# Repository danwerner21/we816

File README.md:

# WE816
The WE816 is a 16-bit 65816 based system with 512K of System RAM, 96K of System ROM, 32K of video RAM, a TMS9918 graphics processor and an AY-3-8910 Sound chip.  The system runs a custom version of BASIC and supports commodore compatible IEC disk drives.

EhBASIC by Lee Davison was ported to the 65816 CPU on the WE816 computer.   It is designed to allow a full 64K bank for BASIC code and variables with the BASIC interpreter running in a totally different bank. Full documentation on the basic intrepreter can be found in the support folder

---

## To Do:

* RTC Hardware (fixed needs PCB created and tested)

* BIOS RTC Code

* Basic Access to RTC

* Fix Video RAM paging

* Document BIOS Calls

---

## What is included in this repo?
As of this time, the repo includes

1. The WE816 Mainboard PCB Kicad design and Gerber files
2. The source code and binaries for the WE816 BASIC interpreter
3. The source code and binaries for the WE816 BIOS firmware
4. The source code and binaries for several hardware test programs
5. The logic equasions for the 3 GALs
6. **OpenSCAD and STL files for a 3d printed case

---

## Known Bugs

 * Note that the Real Time clock circuit on the 8/5/2021 .85 verson of the board is broken and will not work.  The schematic in this repo has been updated to a working version, but this board still has U12 Pin 6 & 7  connected to CB1 & 2 of U36 which has a broken shift register implementation.   I was under the mistaken impression that the shift register bug had been corrected on the WDC version of the 6522, but this is not the case.

### System Jumpers

Jumper P9 -- stereo channel mixer

 *  no jumpers, channel a left, channel c right, channel b left and right
 *  1-2 and 2-3 , channel a,b,c mixed to left and right

Jumper K1 - SRAM chip selection

 * 1&2 - 512K chip used (AS6C4008)
 * 2&3 - 128K chip used (AS6C1008)

Jumper K2 - ROM chip selection

 * 1&2 - 27c256 chip used
 * 2&3 - 29c256 chip used

Jumper K3 - ROM size

 * 1&2 - 16K rom page 0 memory map @ $C000
 * 2&3 - 32K rom page 0 memory map @ $8000

Power P1

 * 1- NC
 * 2-GND
 * 3-GND
 * 4-+5VDC 2A Regulated

Reset P2

 * NO Switch (Short to put system in reset)

Jumper J1, Interrupt Select

* 1&8 UART Interrupt enabled
* 2&7 VIA 1 Interrupt enabled
* 3&6 VIA 2 Interrupt enabled
* 4&5 TMS9918 Interrupt enabled

---

## Bill Of Materials

### Mainboard

Qty|Reference(s)|Value
--------|--------|----------
1|BT1|Battery_Cell
35|C1-C33, C37, C49|0.1 uF
2|C34, C35|33 pF
2|C36, C48|22 uF
1|C38|220 uF
5|C39-C43|1.0 uF
2|C44, C45|270 pF
3|C46, C47, C50|10 uF
1|D1|BICOLOR LED
1|J1|Conn_01x02_Male
1|J2|Conn_01x06_Male
1|J3|Conn_02x08_Counter_Clockwise
1|J4|DIN-5
1|J5|Conn_01x03_Male
1|J6|Conn_02x04_Counter_Clockwise
1|J7|Conn_02x20_Odd_Even
1|J8|AudioJack3
2|J9, J10|DB9_Male
1|K1|Conn_01x03_Male
1|K2|Conn_01x03_Male
1|K3|Conn_01x03_Male
1|L1|INDUCTOR (BEAD)
1|P1|Conn_02x05_Odd_Even
1|P2|Conn_02x02_Odd_Even
1|P3|Screw_Terminal_01x02
1|P4|Conn_01x02_Male
1|P5|Oscillator:CXO_DIP8
1|Q1|2N3904
1|R1|0 ohm
1|R2|470 ohm
2|R3, R4|75 ohm
3|R5, R6, R7|1K ohm
4|R8, R9, R10, R18|1K ohm
5|R11, R12, R13, R14, R17|10K ohm
1|R15|100 ohm
1|R16|10 ohm
1|RR1|1K ohm Bussed 6 pin
2|RR2, RR3|4700 ohm Bussed 6 pin
1|RR4|4700 ohm Bussed 10 pin
2|RV1, RV2|4700 ohm variable
1|U1|74LS393
1|U2|7406
1|U3|74LS06N
1|U4|74F14  (should be F)
1|U5|74LS04
1|U6|TMS9918
1|U7|74LS574
2|U8, U9|74LS574
1|U10|RAM_32KO
1|U11|74LS32
2|U12, U14|GAL16V8 (7ns)
1|U13|GAL20V8 (7ns)
1|U15|16550
1|U16|DS1302
1|U17|MAX232
2|U18, U19|W65C22NxP
5|U20, U22, U23, U24, U31|74LS245
1|U21|74LS244
1|U25|AY-3-8910
1|U26|SRAM_512KO
1|U27|658C16
1|U28|27C256
1|U29|27C512
1|U30|74LS373
1|X1|10.7 MHz
1|X2|CXO_DIP8
1|X3|CRYSTAL 32.768 KHz

### Keyboard
The Keyboard used in the WE816 is identical to the keyboard used in Sergey Kiselev's MSX compatible OMEGA computer.  See the Schematics, PCB layout and build instructions
[here](https://github.com/skiselev/omega/blob/master/Keyboard.md)

### Case
The case in the following images is a 3D print manufactured by the 3D print service offered by JLCPCB.com.  The case was originally designed to be 3D printed by a FDM printer such as the Anycubic Chiron.   It was originally intended that threaded inserts be melted into the stand off posts so the diameter of the holes were sized accordingly.  If a printing service (such as JLCPCB) is used that uses resin printing, it is necessary to slightly drill out the holes in the stand offs so that threaded inserts can be glued in.   It should also be noted that the design tolerances are quite tight and variations in printing can mean that some slight adjusting may be needed in order to get a good fit.

A 12V to 5V converter can be seen in the image that was added into the case in order to convert the 12V power input to the 5B required by the main board.

### Questions?

If there are any questions, I can be reached at vic2020Dan at gmail dot com.

---

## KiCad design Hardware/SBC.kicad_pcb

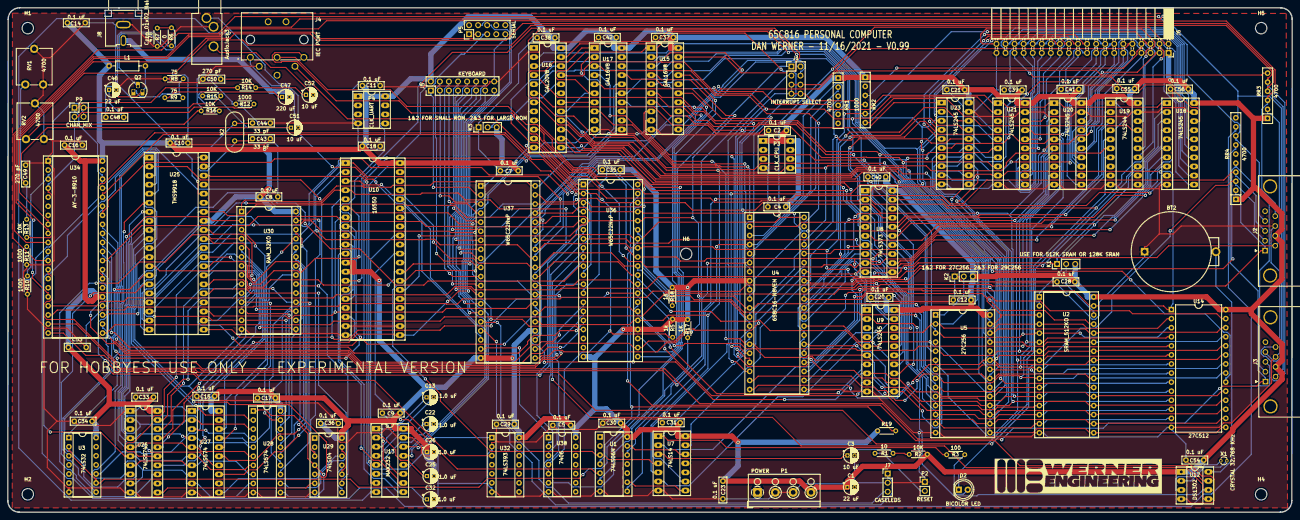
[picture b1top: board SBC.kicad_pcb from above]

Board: 2 copper layers, 360.1 x 141.4 mm, 135 parts (0 on the bottom side), 249 nets.

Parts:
BT2: Battery_Cell; Battery_Holder_Coin_2032_BS-7_FIXED
C1, C46: 22 uF; CP_Radial_D4.0mm_P2.00mm
C2, C4, C5, C7, C8, C9, C10, C11, C12, C14, C15, C16, C17, C18, C20, C21, C23, C28, C29, C30, C31, C33, C34, C35, C36, C37, C38, C39, C40, C41, C42, C48, C53, C54, C55, C56: 0.1 uF; C_Rect_L7.0mm_W2.0mm_P5.00mm
C3, C51, C52: 10 uF; CP_Radial_D4.0mm_P2.00mm
C13, C22, C25, C26, C32: 1.0 uF; CP_Radial_D4.0mm_P2.00mm
C43, C44: 33 pF; C_Rect_L7.0mm_W2.0mm_P5.00mm
C47: 220 uF; CP_Radial_D4.0mm_P2.00mm
C49, C50: 270 pF; C_Rect_L7.0mm_W2.0mm_P5.00mm
D2: BICOLOR LED; LED_D5.0mm
H1, H2, H4, H5, H6: MountingHole; MountingHole_3.2mm_M3
J1: INTERRUPT SELECT; PinHeader_2x04_P2.54mm_Vertical
J2, J3: DB9_Male; DSUB-9_Male_Horizontal_P2.77x2.84mm_EdgePinOffset9.90mm_Hou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
J4: IEC PORT; din6
J5: KEYBOARD; PinHeader_2x08_P2.54mm_Vertical_FIXED
J6: expansion port; PinSocket_2x20_P2.54mm_Horizontal
J7: CASELEDS; PinHeader_1x03_P2.54mm_Vertical
J8: Conn_01x02_Male; CUI_RCJ-041
J9: AudioJack3; Jack_3.5mm_CUI_SJ1-3533NG_Horizontal_CircularHoles
K1: USE FOR 512K SRAM OR 128K SRAM; PinHeader_1x03_P2.54mm_Vertical
K2: 1&2 FOR 27C256, 2&3 FOR 29C256; PinHeader_1x03_P2.54mm_Vertical
K3: 1&2 FOR SMALL ROM, 2&3 FOR LARGE ROM; PinHeader_1x03_P2.54mm_Vertical
L1: INDUCTOR (BEAD); R_Axial_DIN0207_L6.3mm_D2.5mm_P10.16mm_Horizontal
P1: POWER; TerminalBlock_RND_205-00003_1x04_P5.00mm_Horizontal
P2: RESET; PinHeader_1x02_P2.54mm_Vertical
P3: CLK_CPU; DIP-8_W7.62mm_Socket_LongPads
P4: CLK_UART; DIP-8_W7.62mm_Socket_LongPads
P5: SERIAL; PinHeader_2x05_P2.54mm_Vertical
P9: CHAN_MIX; PinHeader_2x02_P2.54mm_Vertical
Q2: 2N3904; TO-92L_HandSolder
R1: 10; R_Axial_DIN0204_L3.6mm_D1.6mm_P5.08mm_Horizontal
R2, R13, R14, R15, R16: 10K; R_Axial_DIN0204_L3.6mm_D1.6mm_P5.08mm_Horizontal
R3: 100; R_Axial_DIN0204_L3.6mm_D1.6mm_P5.08mm_Horizontal
R5: 1k; R_Axial_DIN0204_L3.6mm_D1.6mm_P5.08mm_Horizontal
R6: 0; R_Axial_DIN0204_L3.6mm_D1.6mm_P5.08mm_Horizontal
R7: 470; R_Axial_DIN0204_L3.6mm_D1.6mm_P5.08mm_Horizontal
R8, R9: 75; R_Axial_DIN0204_L3.6mm_D1.6mm_P5.08mm_Horizontal
R10, R11, R12: 1000; R_Axial_DIN0204_L3.6mm_D1.6mm_P5.08mm_Horizontal
R17, R18, R19: 1K; R_Axial_DIN0204_L3.6mm_D1.6mm_P5.08mm_Horizontal
RR1, RR3: 4700; R_Array_SIP6
RR2: 1000; R_Array_SIP6
RR4: 4700; R_Array_SIP10
RV1, RV2: 4700; Potentiometer_ACP_CA9-V10_Vertical
U1: 74LS06N; DIP-14_W7.62mm_Socket
U2: SRAM_512KO; DIP-32_W15.24mm_Socket
U3: 74LS32; DIP-14_W7.62mm_Socket
U4: 658C16-N8VEM; DIP-40_W15.24mm_Socket
U5: 27C256; DIP-28_W15.24mm_Socket
U7: 74LS14; DIP-14_W7.62mm_Socket_LongPads
U8: 74LS373; DIP-20_W7.62mm_Socket_LongPads
U9, U18, U20, U21, U23: 74LS245; DIP-20_W7.62mm_Socket_LongPads
U10: 16550; DIP-40_W15.24mm_Socket_LongPads
U12: DS1302; DIP-8_W7.62mm_Socket_LongPads
U13: MAX232; DIP-16_W7.62mm_Socket_LongPads
U14: 27C512; DIP-28_W15.24mm
U15, U17: GAL16V8; DIP-20_W7.62mm_Socket_LongPads
U16: GAL20V8; DIP-24_W7.62mm_Socket_LongPads
U19: 74LS244; DIP-20_W7.62mm_Socket_LongPads
U25: TMS9918; DIP-40_W15.24mm_Socket_LongPads
U26, U27: 74LS574; DIP-20_W7.62mm_Socket_LongPads
U28: 74LS574; DIP-20_W7.62mm_Socket
U29: 74LS04; DIP-14_W7.62mm_Socket
U30: RAM_32KO; DIP-28_W15.24mm_Socket
U32: 74LS393; DIP-14_W7.62mm_Socket
U34: AY-3-8910; DIP-40_W15.24mm_Socket
U36, U37: W65C22NxP; DIP-40_W15.24mm_Socket
U38: 7406; DIP-14_W7.62mm_Socket
X1: CRYSTAL 32.768 KHz; Crystal_Round_D1.5mm_Vertical
X2: 10.7 MHz; Crystal_HC18-U_Vertical

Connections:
/Video/COMVID: C47.2, J8.2
A0: U2.12, U4.9, U5.10, U10.28, U14.10, U15.2, U20.2, U25.13, U36.38, U37.38
A1: U2.11, U4.10, U5.9, U10.27, U14.9, U15.3, U20.3, U36.37, U37.37
A2: U2.10, U4.11, U5.8, U10.26, U14.8, U15.4, U20.4, U36.36, U37.36
A3: U2.9, U4.12, U5.7, U14.7, U15.5, U20.5, U36.35, U37.35
A4: U2.8, U4.13, U5.6, U14.6, U15.6, U20.6
A5: U2.7, U4.14, U5.5, U14.5, U15.7, U20.7
A6: U2.6, U4.15, U5.4, U14.4, U15.8, U20.8
A7: U2.5, U4.16, U5.3, U14.3, U15.9, U20.9
A8: U2.27, U4.17, U5.25, U14.25, U16.21, U21.2
A9: U2.26, U4.18, U5.24, U14.24, U16.22, U21.3
A10: U2.23, U4.19, U5.21, U14.21, U16.2, U21.4
A11: U2.25, U4.20, U5.23, U14.23, U16.3, U21.5
A12: U2.4, U4.22, U5.2, U14.2, U16.4, U21.6
A13: U2.28, U4.23, U5.26, U14.26, U16.5, U21.7
A14: U2.3, U4.24, U5.27, U14.27, U16.6, U21.8
A15: U2.31, U4.25, U14.1, U16.7, U21.9
A16: U2.2, U8.2, U16.8, U18.2
A17: K1.1, U8.5, U16.9, U18.3
A18: U2.1, U8.6, U16.10, U18.4
A19: U8.9, U16.11, U18.5
A20: U8.12, U16.14, U18.6
A21: U8.15, U16.1, U18.7
A22: U8.16, U16.13, U18.8
A23: U8.19, U16.23, U18.9
ABORT: RR1.4, U4.3
AD0: U4.33, U8.3, U9.18
AD1: U4.32, U8.4, U9.17
AD2: U4.31, U8.7, U9.16
AD3: U4.30, U8.8, U9.15
AD4: U4.29, U8.13, U9.14
AD5: U4.28, U8.14, U9.13
AD6: U4.27, U8.17, U9.12
AD7: U4.26, U8.18, U9.11
BUS: U16.18, U17.7
BUSAK: U17.17, U18.1, U20.1, U21.1
BUSRQ: U4.36, U19.3
B_A0: J6.3, U20.18
B_A1: J6.5, U20.17
B_A2: J6.7, U20.16
B_A3: J6.9, U20.15
B_A4: J6.11, U20.14
B_A5: J6.13, U20.13
B_A6: J6.15, U20.12
B_A7: J6.17, U20.11
B_A8: J6.19, U21.18
B_A9: J6.21, U21.17
B_A10: J6.23, U21.16
B_A11: J6.25, U21.15
B_A12: J6.27, U21.14
B_A13: J6.29, U21.13
B_A14: J6.31, U21.12
B_A15: J6.33, U21.11
B_A16: J6.35, U18.18
B_A17: J6.37, U18.17
B_A18: J6.38, U18.16
B_A19: J6.36, U18.15
B_A20: J6.34, U18.14
B_A21: J6.32, U18.13
B_A22: J6.30, U18.12
B_A23: J6.28, U18.11
B_BUSRQ: RR2.6, U19.17
B_CLK_CPU: J6.4, U19.14
B_D0: J6.26, U23.2
B_D1: J6.24, U23.3
B_D2: J6.22, U23.4
B_D3: J6.20, U23.5
B_D4: J6.18, U23.6
B_D5: J6.16, U23.7
B_D6: J6.14, U23.8
B_D7: J6.12, U23.9
B_INT: J1.5, J1.6, J1.7, J1.8, J6.10, RR2.4, U7.9
B_NMI: J6.6, RR2.5, U7.13
B_RW: J6.40, U19.18
B_WAIT: J6.8, RR2.3, U19.15
CLK_AUDIO: U25.38, U32.1
CLK_CPU: P3.5, U4.37, U7.5, U17.1, U19.6, U36.25, U37.25
CLK_UART: P4.5, U10.16
COLUMN0: J5.1, U37.2
COLUMN1: J5.2, U37.3
COLUMN2: J5.3, U37.4
COLUMN3: J5.4, U37.5
COLUMN4: J5.5, U37.6
COLUMN5: J5.6, U37.7
COLUMN6: J5.7, U37.8
COLUMN7: J5.8, U37.9
COMP_VID: R6.2, U25.36
CS_RAM: U2.22, U16.16
CS_ROM: U5.20, U16.15
CS_UART: U10.14, U15.19
CS_VDP: U3.2, U3.9, U15.17
CS_VIA1: U15.15, U36.23
CS_VIA2: U15.14, U37.23
CTS: P5.6, U13.13
CTS_TTL: U10.36, U13.12
D0: U2.13, U5.11, U9.2, U10.1, U14.11, U23.18, U25.17, U36.33, U37.33
D1: U2.14, U5.12, U9.3, U10.2, U14.12, U23.17, U25.18, U36.32, U37.32
D2: U2.15, U5.13, U9.4, U10.3, U14.13, U23.16, U25.19, U36.31, U37.31
D3: U2.17, U5.15, U9.5, U10.4, U14.15, U23.15, U25.20, U36.30, U37.30
D4: U2.18, U5.16, U9.6, U10.5, U14.16, U23.14, U25.21, U36.29, U37.29
D5: U2.19, U5.17, U9.7, U10.6, U14.17, U23.13, U25.22, U36.28, U37.28
D6: U2.20, U5.18, U9.8, U10.7, U14.18, U23.12, U25.23, U36.27, U37.27
D7: U2.21, U5.19, U9.9, U10.8, U14.19, U23.11, U25.24, U36.26, U37.26
DATA_DIR: U17.14, U23.1
EMU: R3.2, U4.35, U7.1
GND: BT2.2, C1.2, C2.2, C3.2, C4.2, C5.2, C7.2, C8.2, C9.2, C10.2, C11.2, C12.2, C14.2, C15.2, C16.2, C17.2, C18.2, C20.2, C21.2, C23.2, C26.2, C28.2, C29.2, C30.2, C31.2, C32.2, C33.2, C34.2, C35.2, C36.2, C37.2, C38.2, C39.2, C40.2, C41.2, C42.2, C43.2, C44.2, C46.2, C48.2, C49.1, C50.2, C53.2, C54.2, C55.2, C56.2, J2.8, J3.8, J4.2, J5.9, J6.39, J7.2, J8.1, J9.T, K2.1, K3.1, P1.2, P1.3, P2.1, P3.4, P4.4, P5.9, R7.2, R8.2, R10.2, R11.2, R12.2, RV1.1, RV1.2, RV2.1, RV2.2, U1.7, U2.16, U3.7, U4.21, U5.14, U7.7, U8.1, U8.10, U9.10, U10.19, U10.20, U10.22, U10.25, U12.4, U13.15, U14.14, U15.10, U16.12, U17.10, U18.10, U18.19, U19.1, U19.10, U19.19, U20.10, U20.19, U21.10, U21.19, U23.10, U23.19, U25.12, U26.1, U26.10, U27.1, U27.10, U28.10, U29.7, U30.14, U32.2, U32.7, U34.1, U34.24, U36.1, U37.1, U38.7
INT: RR1.2, U1.8, U4.4
IO: U15.1, U16.17, U17.6
KB_CAPS_LED: J5.11, U37.14
KB_GRAPH_LED: J5.10, U37.15
LED_1: J7.3, U37.16
LED_2: J7.1, U37.17
LED_ANODE: D2.1, U19.7
ML: U4.5, U17.5
NMI: RR1.3, U1.12, U4.6
N_EMU: U7.2, U19.13
unnamed: BT2.1, U12.8
unnamed: C3.1, R1.1, R2.2, U7.3
unnamed: C13.1, U13.1
unnamed: C13.2, U13.3
unnamed: C22.1, U13.4
unnamed: C22.2, U13.5
unnamed: C25.1, U13.2
unnamed: C32.1, U13.6
unnamed: C43.1, U25.40, X2.1
unnamed: C44.1, U25.39, X2.2
unnamed: C46.1, C48.1, L1.2, Q2.3
unnamed: C47.1, R9.2
unnamed: C49.2, C51.1, R13.1, R15.2, RV1.3
unnamed: C50.1, C52.1, R14.1, R16.2, RV2.3
unnamed: C51.2, J9.S
unnamed: C52.2, J9.R
unnamed: D2.2, R3.1
unnamed: J1.1, U1.6
unnamed: J4.3, R17.2, U38.6
unnamed: K1.2, U2.30
unnamed: K2.2, U5.1
unnamed: K3.2, U16.20
unnamed: P2.2, R1.2
unnamed: P9.1, R11.1, R14.2, U34.38
unnamed: P9.2, P9.4, R10.1, R15.1, R16.1, U34.3
unnamed: P9.3, R12.1, R13.2, U34.4
unnamed: Q2.1, R8.1, R9.1
unnamed: Q2.2, R6.1, R7.1
unnamed: U1.9, U7.8
unnamed: U1.13, U7.12
unnamed: U7.6, U8.11, U9.19
unnamed: U10.9, U10.15
unnamed: U12.2, X1.2
unnamed: U12.3, X1.1
unnamed: U26.13, U30.4
unnamed: U26.14, U30.5
unnamed: U26.15, U30.6
unnamed: U26.16, U30.7
unnamed: U26.17, U30.8
unnamed: U26.18, U30.9
unnamed: U26.19, U30.10
unnamed: U27.13, U30.26
unnamed: U27.14, U30.2
unnamed: U27.15, U30.23
unnamed: U27.16, U30.21
unnamed: U27.17, U30.24
unnamed: U27.18, U30.25
unnamed: U27.19, U30.3
unnamed: U29.10, U29.13
unnamed: U29.8, U29.11
unnamed: U32.3, U34.22
O1_ROM: U14.20, U16.19
P1_A: J2.6, RR3.2, U34.17
P1_B: J2.9, RR3.3, U34.16
P1_D: J2.2, RR4.3, U34.20
P1_L: J2.3, RR4.4, U34.19
P1_R: J2.4, RR4.5, U34.18
P1_U: J2.1, RR4.2, U34.21
P2_A: J3.6, RR3.4, U34.9
P2_B: J3.9, RR3.5, U34.8
P2_D: J3.2, RR4.8, U34.12
P2_L: J3.3, RR4.9, U34.11
P2_R: J3.4, RR4.10, U34.10
P2_U: J3.1, RR4.7, U34.13
RD: U2.24, U3.10, U5.22, U10.21, U14.22, U17.16
RESET: J6.2, R19.2, U1.4, U4.40, U25.34, U34.23, U36.34, U37.34
ROWA: J5.15, U37.10
ROWB: J5.14, U37.11
ROWC: J5.13, U37.12
ROWD: J5.12, U37.13
RTS: P5.4, U13.14
RTS_TTL: U10.32, U13.11
RW: U4.34, U9.1, U17.2, U19.2, U36.22, U37.22
RX: P5.3, U13.8
SERATNOUT: U36.9, U38.5
SERCLKIN: J4.4, R5.2, U36.2, U38.4
SERCLKOUT: U37.39, U38.3
SERDATAIN: J4.5, R18.2, U36.3, U38.2
SERDATAOUT: U37.19, U38.1
SERSRQ: J4.1, U37.18
SIN_TTL: U10.10, U13.9
SOUT_TTL: U10.11, U13.10
TX: P5.5, U13.7
UART_INT: U1.5, U10.30
URESET: U1.3, U7.4, U10.35
USERA_2: U34.27, U36.4
USERA_3: U34.29, U36.5
USERA_4: U34.28, U36.6
USERA_5: U12.6, U36.7
USERA_6: U12.5, U36.8
USERB_0: U34.37, U36.10
USERB_1: U34.36, U36.11
USERB_2: U34.35, U36.12
USERB_3: U34.34, U36.13
USERB_4: U34.33, U36.14
USERB_5: U34.32, U36.15
USERB_6: U34.31, U36.16
USERB_7: U34.30, U36.17
USERCA_2: U12.7, U36.39
VAD0: U25.10, U28.2
VAD1: U25.9, U26.2, U27.2, U28.3
VAD2: U25.8, U26.3, U27.3, U28.4
VAD3: U25.7, U26.4, U27.4, U28.5
VAD4: U25.6, U26.5, U27.5, U28.6
VAD5: U25.5, U26.6, U27.6, U28.7
VAD6: U25.4, U26.7, U27.7, U28.8
VAD7: U25.3, U26.8, U26.9, U27.8, U27.9, U28.9
VCAS: U25.2, U29.9, U30.20
VCC: C1.1, C2.1, C4.1, C5.1, C7.1, C8.1, C9.1, C10.1, C11.1, C12.1, C14.1, C15.1, C16.1, C17.1, C18.1, C20.1, C21.1, C23.1, C25.2, C26.1, C28.1, C29.1, C30.1, C31.1, C33.1, C34.1, C35.1, C36.1, C37.1, C38.1, C39.1, C40.1, C41.1, C42.1, C53.1, C54.1, C55.1, C56.1, J2.7, J3.7, J5.16, J6.1, K1.3, K2.3, K3.3, L1.1, P1.4, P3.1, P3.8, P4.1, P4.8, R2.1, R5.1, R17.1, R18.1, R19.1, RR1.1, RR2.1, RR3.1, RR4.1, U1.14, U2.32, U3.14, U4.8, U5.28, U7.14, U8.20, U9.20, U10.12, U10.13, U10.40, U12.1, U13.16, U14.28, U15.20, U16.24, U17.20, U18.20, U19.20, U20.20, U21.20, U23.20, U25.33, U26.20, U27.20, U28.20, U29.14, U30.28, U32.14, U34.25, U34.40, U36.20, U36.24, U37.20, U37.24, U38.14
VCOL: U27.11, U29.12
VD0: U25.32, U28.19, U30.11
VD1: U25.31, U28.18, U30.12
VD2: U25.30, U28.17, U30.13
VD3: U25.29, U28.16, U30.15
VD4: U25.28, U28.15, U30.16
VD5: U25.27, U28.14, U30.17
VD6: U25.26, U28.13, U30.18
VD7: U25.25, U28.12, U30.19
VDA: U4.39, U17.3
VDPRD: U3.8, U25.15
VDPWR: U3.3, U25.14
VIA1_INT: J1.2, U36.21
VIA2_INT: J1.3, U37.21
VP: U4.1, U17.8
VPA: U4.7, U17.4
VRAM_BANK: RR3.6, U30.1, U37.40
VRAS: U25.1, U29.5
VRD: U28.11, U29.4, U30.22
VROW: U26.11, U29.6
VRW: U25.11, U28.1, U29.3, U30.27
V_INT: J1.4, U25.16
WAIT: U4.2, U19.5
WR: U2.29, U3.1, U10.18, U17.15

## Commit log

2022-01-20 case
2022-01-22 Add keyboard bounce adjustment
2022-09-05 doc update
